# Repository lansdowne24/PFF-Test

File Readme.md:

Project file and associated documents are located at the first level.  Individual final submission files are in the "Final Submission Files" folder.

Please let me know if you need anything else!  (Also, my expertise is in Altium, and I have experience with Cadence Allegro from a previous place of emplyoment.  Would be happy to demonstrate this process in either if need be!)

Mike Roberts
lansdowne24@gmail.com
603-289-9423

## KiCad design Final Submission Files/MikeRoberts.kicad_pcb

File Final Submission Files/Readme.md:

Final submission files are in the "Final submission folder".  The rest of the items are working project files.

Please let me know if you need anything else!  (Also, my expertise is in Altium, and I have experience with Cadence Allegro from a previous place of emplyoment.  Would be happy to demonstrate this process in either if need be!)

Mike Roberts
lansdowne24@gmail.com
603-289-9423

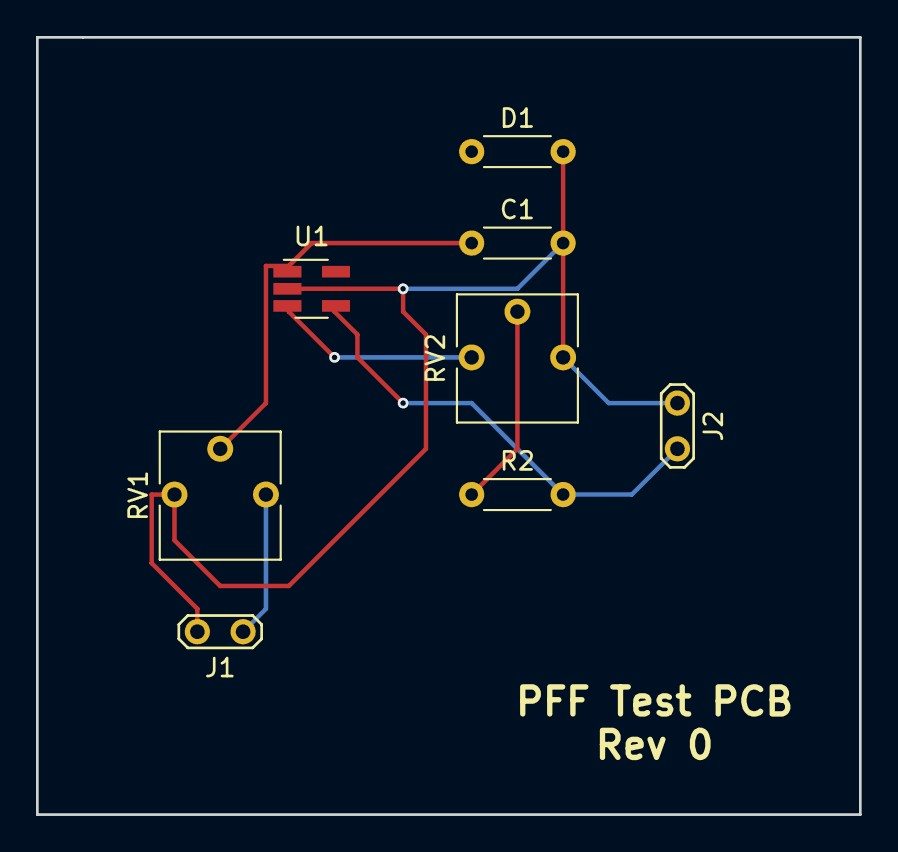
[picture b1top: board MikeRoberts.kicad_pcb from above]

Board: 2 copper layers, 45.7 x 43.2 mm, 8 parts (0 on the bottom side), 6 nets.

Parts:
C1: 0.1uF; R_Axial_DIN0204_L3.6mm_D1.6mm_P5.08mm_Horizontal
D1: 2.1V; R_Axial_DIN0204_L3.6mm_D1.6mm_P5.08mm_Horizontal
J1: INPUT HEADER; Test_Point_2Pads
J2: OUTPUT HEADER; Test_Point_2Pads
R2: 15k; R_Axial_DIN0204_L3.6mm_D1.6mm_P5.08mm_Horizontal
RV1, RV2: POT; Potentiometer_Trimmer_Vishay_T73YP_Horizontal
U1: LM321; SOT-23-5_HandSoldering

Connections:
/VOUT: J2.2, R2.2, U1.4
GND: C1.2, D1.2, J1.2, J2.1, RV1.3, RV2.1, U1.2
Input: J1.1, RV1.1
unnamed: C1.1, RV1.2, U1.1
unnamed: R2.1, RV2.2
unnamed: RV2.3, U1.3

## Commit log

2017-03-29 :neckbeard: Added .gitattributes & .gitignore files
2017-03-29 First addition of PFF Project Files
    First addition of PFF Project Files
2017-03-29 Updating for Final Submission Folder
    Updating for Final Submission Folder
2017-03-29 Final push
    Updated schematics + layout files
2017-03-29 Update Readme
    Update Readme
